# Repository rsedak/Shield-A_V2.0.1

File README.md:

[Croatian version](README_HR-HR.md). 

Introduction
============

Shield-A v2.0.1 is version of Arduino Uno based shield for student education compatible with BASCOM-AVR(C) and Arduino IDE.
During programming please keep in mind next design rules:
- D0-D7 — LEDs can be used only if D12 is set to OUTPUT HIGH state
- LCD 1602 — can be used only if A3 is set to OUTPUT HIGH state
- RGB LED — are connected in matrix (D5-D7 - colors; D8-D11 - LEDs)
- D12 — enables D0-D7 LEDs
- D13 — reserved for buzzer
- A0 — reserved for potentiometer
- A1,A2 — reserved for switch in INPUT_PULLUP mode
- A3 — enables LCD 1602 back-light
- A4,A5 — reserved for I2C communication with on board pull-up resistors

Contributors
------------
- Vladimir Mitrović — features, BASCOM-AVR expertise
- Robert Sedak — features, Arduino expertise, schematic design, CAD design. 

Application
-----------

You can download examples for Arduino IDE from [here](examples/). 
Examples which name ends with '_R' are solution with register maniputalion.

Bill Of Materials
-----------------
- 1 ea., PCB
- 8 ea., 220 ohm 1/4W 1% Resistor 1206 (R1-R8)
- 2 ea., 100 ohm 1/4W 1% Resistor 1206 (R9, R10)
- 1 ea., 2.7K ohm 1/4W 1% Resistor 1206 (R11)
- 1 ea., 1.8K ohm 1/4W 1% Resistor 1206 (R12)
- 1 ea., 3.9K ohm 1/4W 1% Resistor 1206 (R13)
- 4 ea., 10K ohm 1/4W 1% Resistor 1206 (R14, R15, R17, R18)
- 1 ea., 18 ohm 1/4W 1% Resistor 1206 (R16)
- 8 ea., LED 3528 (D0-D7)
- 4 ea., RGB LED RS-3535MWAR (D8-D11)
- 1 ea., 14x7.5mm passive electronic piezoelectric buzzer SE
- 2 ea., MOSFET MMBF170 SOT-23
- 1 ea., 3386-P 10K potentiometer with knob
- 1 ea., 3386-P 10K potentiometer without knob
- 1 ea., 2.54mm pitch slide DIP switch 2-bit
- 1 ea., 6x6x4.3mm SPST Momentary push switch
- 2 ea., 6x6x10mm SPST Momentary push switch
- 1 ea., 1x16Pin 2.54mm Straight Pin Header - Black
- 1 ea., 1x10Pin 2.54mm Straight Pin Header - Black
- 2 ea., 1x8Pin 2.54mm Straight Pin Header - Black
- 1 ea., 1x6Pin 2.54mm Straight Pin Header - Black
- 1 ea., 1x4 pin 2.54mm Socket Connector
- 1 ea., 1x16 pin 2.54mm Socket Connector
- 1 ea., LCD 1602 HD44780 (pin 15 is anode, pin 16 is katode)

Design Files
------------
This project is designed using Open Source [KiCad](http://kicad.org/). Design files are located in the [design_files](design_files/) folder.  You can see the [schematic](images/shield_a_v2.0.1_schematic.png).

Production files
------------
You can download gerber files from [here](gerber/shield-a_v.2.0.1.zip).
You can download BOM file from [here](gerber/shield-a_v.2.0.1_bom_top.csv).
You can download centorid file from [here](gerber/shield-a_v.2.0.1-top-pos.csv).

Firmware
--------
This project can be programmed using the Open Source [Arduino](https://www.arduino.cc/) and [BASCOM-AVR(C)](https://www.mcselec.com/index.php?option=com_content&task=view&id=14&Itemid=103).
Arduino examples are located in [examples](examples/) folder.

License
-------
[Attribution-ShareAlike 4.0 International (CC BY-SA 4.0)](https://creativecommons.org/licenses/by-sa/4.0/)

You are free to:
- Share — copy and redistribute the material in any medium or format
- Adapt — remix, transform, and build upon the material

This license is acceptable for Free Cultural Works.
- The licensor cannot revoke these freedoms as long as you follow the license terms.

Under the following terms:
- Attribution — You must give appropriate credit, provide a link to the license, and indicate if changes were made. You may do so in any reasonable manner, but not in any way that suggests the licensor endorses you or your use.
- ShareAlike — If you remix, transform, or build upon the material, you must distribute your contributions under the same license as the original.

No additional restrictions — You may not apply legal terms or technological measures that legally restrict others from doing anything the license permits.

Reference Designs ARE PROVIDED "AS IS" AND "WITH ALL FAULTS". Authors DISCLAIMS ALL OTHER WARRANTIES, EXPRESS OR IMPLIED, REGARDING PRODUCTS, INCLUDING BUT NOT LIMITED TO, ANY IMPLIED WARRANTIES OF MERCHANTABILITY OR FITNESS FOR A PARTICULAR PURPOSE.
Authors may make changes to specifications and product descriptions at any time, without notice. The Customer must notrely on the absence or characteristics of any features or instructions marked "reserved" or "undefined." 
Authors reservesthese for future definition and shall have no responsibility whatsoever for conflicts or incompatibilities arising from future changes to them. The product information on the Web Site or Materials is subject to change without notice. Do not finalize a design with this info.

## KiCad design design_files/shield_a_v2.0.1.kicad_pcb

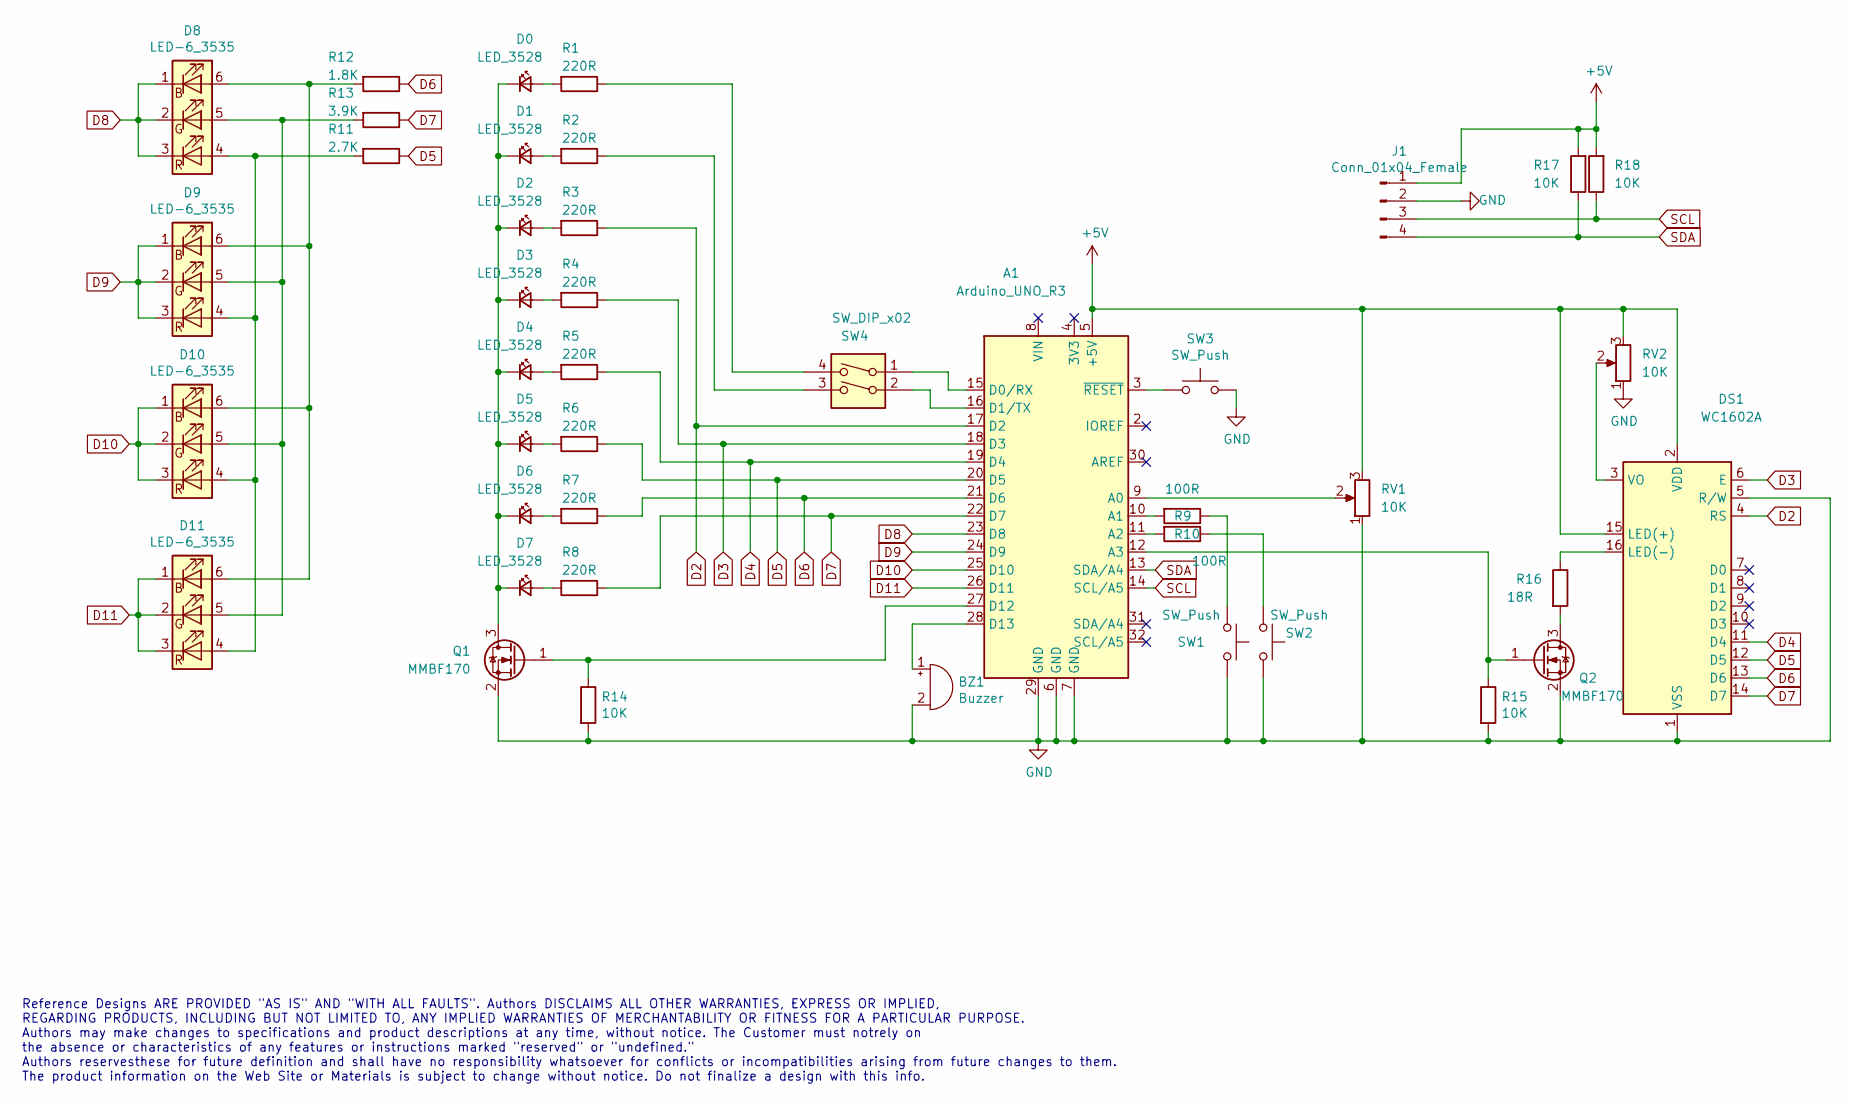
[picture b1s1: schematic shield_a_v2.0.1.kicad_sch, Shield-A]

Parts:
A1: Arduino_UNO_R3
BZ1: Buzzer; Buzzer_12x9.5RM7.6_5; LCSC C417411
D0, D1, D2, D3, D4, D5, D6, D7: LED_3528; LED_3528_Hubei_Kento_Elec; LCSC C335779
D8, D9, D10, D11: LED-6_3535; RS-3535MWAR; LCSC C110402
DS1: WC1602A; PinSocket_1x16_P2.54mm_Vertical; LCSC C66987
J1: Conn_01x04_Female; PinSocket_1x04_P2.54mm_Horizontal; LCSC C225512
Q1, Q2: MMBF170; SOT-23; LCSC C130879
R1, R2, R3, R4, R5, R6, R8: 220R; R_1206_3216Metric; LCSC C17957
R7: 220R; R_1206_3216Metric; JLC 1206
R9, R10: 100R; R_1206_3216Metric; LCSC C17901
R11: 2.7K; R_1206_3216Metric; LCSC C17950
R12: 1.8K; R_1206_3216Metric; LCSC C22108
R13: 3.9K; R_1206_3216Metric; LCSC C17883
R14, R15, R17, R18: 10K; R_1206_3216Metric; LCSC C17902
R16: 18R; R_1206_3216Metric; LCSC C17922
RV1: 10K; Potentiometer_Bourns_3386P_Vertical; LCSC C330455
RV2: 10K; Potentiometer_Bourns_3386P-2_Vertical; LCSC C118953
SW1, SW2: SW_Push; SW_SMD_PUSH_6mm_h7mm; LCSC C780516
SW3: SW_Push; SW_SMD_PUSH_6mm_h4.3mm; LCSC C780510
SW4: SW_DIP_x02; SW_DIP_SPSTx02_Slide_Dungguan-Guangzhu-Industrial_DIS02LSGE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; LCSC C54949

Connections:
+5V: A1.5 (+5V), DS1.2 (VDD), DS1.15 (LED(+)), J1.1, R17.2, R18.2, RV1.3, RV2.3
D2: A1.17 (D2), DS1.4 (RS), R3.1
D3: A1.18 (D3), DS1.6 (E), R4.1
D4: A1.19 (D4), DS1.11 (D4), R5.1
D5: A1.20 (D5), DS1.12 (D5), R6.1, R11.1
D6: A1.21 (D6), DS1.13 (D6), R7.1, R12.1
D7: A1.22 (D7), DS1.14 (D7), R8.1, R13.1
D8: A1.23 (D8), D8.1 (BK), D8.2 (GK), D8.3 (RK)
D9: A1.24 (D9), D9.1 (BK), D9.2 (GK), D9.3 (RK)
D10: A1.25 (D10), D10.1 (BK), D10.2 (GK), D10.3 (RK)
D11: A1.26 (D11), D11.1 (BK), D11.2 (GK), D11.3 (RK)
GND: A1.6 (GND), A1.7 (GND), A1.29 (GND), BZ1.2 (+), DS1.1 (VSS), DS1.5 (R/W), J1.2, Q1.2 (S), Q2.2 (S), R14.2, R15.2, RV1.1, RV2.1, SW1.2, SW2.2, SW3.2
unnamed: A1.3 (~RESET), SW3.1
unnamed: A1.9 (A0), RV1.2
unnamed: A1.10 (A1), R9.2
unnamed: A1.11 (A2), R10.2
unnamed: A1.12 (A3), Q2.1 (G), R15.1
unnamed: A1.15 (D0/RX), SW4.1
unnamed: A1.16 (D1/TX), SW4.2
unnamed: A1.27 (D12), Q1.1 (G), R14.1
unnamed: A1.28 (D13), BZ1.1 (-)
unnamed: D0.1 (K), D1.1 (K), D2.1 (K), D3.1 (K), D4.1 (K), D5.1 (K), D6.1 (K), D7.1 (K), Q1.3 (D)
unnamed: D0.2 (A), R1.2
unnamed: D1.2 (A), R2.2
unnamed: D2.2 (A), R3.2
unnamed: D3.2 (A), R4.2
unnamed: D4.2 (A), R5.2
unnamed: D5.2 (A), R6.2
unnamed: D6.2 (A), R7.2
unnamed: D7.2 (A), R8.2
unnamed: D8.4 (RA), D9.4 (RA), D10.4 (RA), D11.4 (RA), R11.2
unnamed: D8.5 (GA), D9.5 (GA), D10.5 (GA), D11.5 (GA), R13.2
unnamed: D8.6 (BA), D9.6 (BA), D10.6 (BA), D11.6 (BA), R12.2
unnamed: DS1.3 (VO), RV2.2
unnamed: DS1.16 (LED(-)), R16.1
unnamed: Q2.3 (D), R16.2
unnamed: R1.1, SW4.4
unnamed: R2.1, SW4.3
unnamed: R9.1, SW1.1
unnamed: R10.1, SW2.1
SCL: A1.14 (SCL/A5), J1.3, R18.1
SDA: A1.13 (SDA/A4), J1.4, R17.1

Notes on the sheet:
Reference Designs ARE PROVIDED "AS IS" AND "WITH ALL FAULTS". Authors DISCLAIMS ALL OTHER WARRANTIES, EXPRESS OR IMPLIED, REGARDING PRODUCTS, INCLUDING BUT NOT LIMITED TO, ANY IMPLIED WARRANTIES OF MERCHANTABILITY OR FITNESS FOR A PARTICULAR PURPOSE. Authors may make changes to specifications and p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

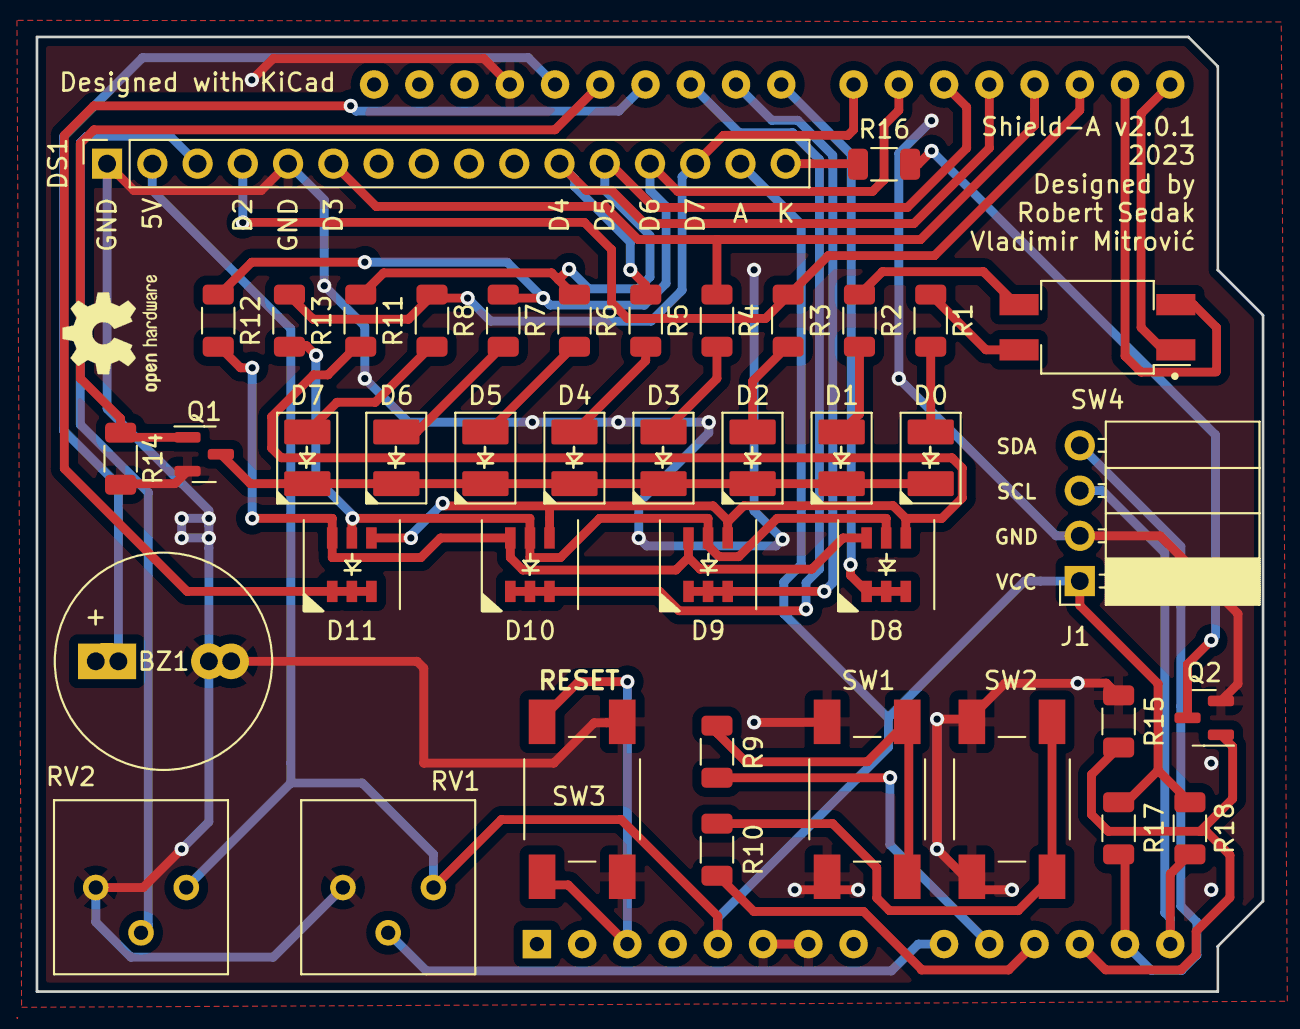
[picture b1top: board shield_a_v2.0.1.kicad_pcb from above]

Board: 2 copper layers, 68.8 x 53.6 mm, 42 parts (1 on the bottom side), 42 nets.

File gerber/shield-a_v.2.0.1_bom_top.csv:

"Comment","Designator","Footprint","LCSC Part #"
"LED_3528","D0 D1 D2 D3 D4 D5 D6 D7","LED_3528","C335779"
"LED-6_3535","D8 D9 D10 D11","LED-6_3535","C110402"
"MMBF170","Q1 Q2","SOT-23","C130879"
"220R","R1 R2 R3 R4 R5 R6 R7 R8","1206","C17957"
"100R","R9 R10","1206","C17901"
"2.7K","R11","1206","C17950"
"1.8K","R12","1206","C22108"
"3.9K","R13","1206","C17883"
"10K","R14 R15 R17 R18","1206","C17902"
"18R","R16","1206","C17922"
"SW_Push","SW1 SW2","SMD","C780516"
"SW_Push","SW3","SW-SMD","C780510"
"SW_DIP_x02","SW4","SMD","C54949"

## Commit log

2023-12-14 Adding schematic in PDF

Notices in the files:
design_files/shield_a_v2.0.1.kicad_pcb:
License: CC-BY-SA 4.0
